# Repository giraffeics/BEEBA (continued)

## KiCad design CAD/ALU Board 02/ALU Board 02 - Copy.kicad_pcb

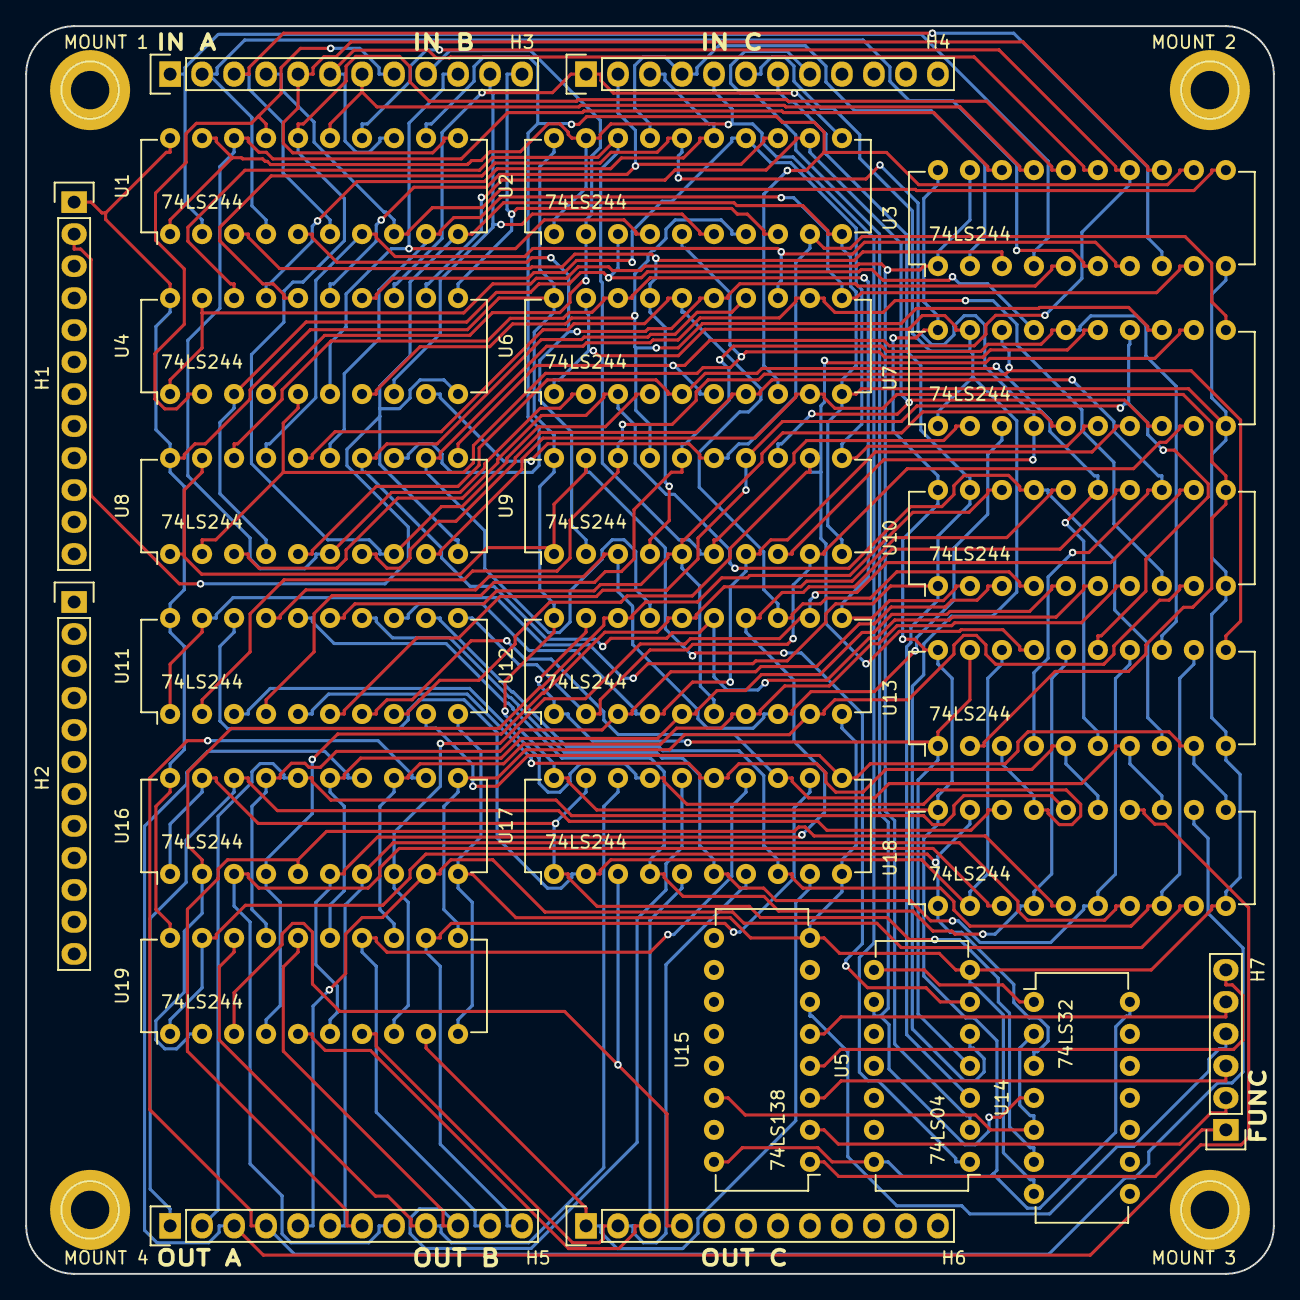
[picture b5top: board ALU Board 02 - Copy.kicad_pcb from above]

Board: 2 copper layers, 99.1 x 99.1 mm, 30 parts (0 on the bottom side), 99 nets.

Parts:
H1, H2, H3, H4, H5, H6: CONN_01X12; Socket_Strip_Straight_1x12
H7: CONN_01X06; Socket_Strip_Straight_1x06
MOUNT 1, MOUNT 2, MOUNT 3, MOUNT 4: 1pin
U1, U2, U3, U4, U6, U7, U8, U9, U10, U11, U12, U13, U16, U17, U18, U19: 74LS244; DIP-20_W7.62mm
U5: 74LS04; DIP-14_W7.62mm
U14: 74LS32; DIP-14_W7.62mm
U15: 74LS138; DIP-16_W7.62mm

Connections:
FS09: U14.2, U14.5, U15.14
FUNC0: H7.1, U15.1
FUNC1: H7.2, U15.2
FUNC2: H7.3, U15.3
FUNC3: H7.4, U15.6
FUNC4: H7.5, U15.5
FUNC5: H7.6, U15.4
GND: H1.2, U1.10, U2.10, U3.10, U4.10, U5.7, U6.10, U7.10, U8.10, U9.10, U10.10, U11.10, U12.10, U13.10, U14.7, U15.8, U16.10, U17.10, U18.10, U19.10
INA0: H3.1, U1.2, U3.4
INA1: H3.2, U1.4, U3.6
INA2: H3.3, U1.6, U3.8
INA3: H3.4, U1.8, U3.11
INA4: H3.5, U1.11, U3.13
INA5: H3.6, U1.13, U3.15
INA6: H3.7, U1.15, U3.17
INA7: H3.8, U1.17, U4.2
INB0: H3.9, U2.2, U4.4
INB1: H3.10, U2.4, U4.6
INB2: H3.11, U2.6, U4.8
INB3: H3.12, U2.8, U4.11
INB4: H4.1, U2.11, U4.13
INB5: H4.2, U2.13, U4.15
INB6: H4.3, U2.15, U4.17
INB7: H4.4, U2.17, U3.2
INC0: H4.5, U1.1, U1.19, U2.1, U2.19, U5.1
INC1: H4.6, U5.5, U6.1, U6.19, U7.1, U7.19
INC2: H4.7, U5.3, U10.1, U10.19, U11.1, U11.19
INC3: H4.8, U5.9, U14.4
NINC0: U3.1, U3.19, U4.1, U4.19, U5.2
NINC1: U5.6, U8.1, U8.19, U9.1, U9.19
NINC2: U5.4, U12.1, U12.19, U13.1, U13.19
NINC3: U14.3, U18.1, U18.19, U19.1, U19.19
unnamed: U5.8, U14.1
OUTA0: H5.1, U16.18, U18.18
OUTA1: H5.2, U16.16, U18.16
OUTA2: H5.3, U16.14, U18.14
OUTA3: H5.4, U16.12, U18.12
OUTA4: H5.5, U16.9, U18.9
OUTA5: H5.6, U16.7, U18.7
OUTA6: H5.7, U16.5, U18.5
OUTA7: H5.8, U16.3, U18.3
OUTB0: H5.9, U17.18, U19.18
OUTB1: H5.10, U17.16, U19.16
OUTB2: H5.11, U17.14, U19.14
OUTB3: H5.12, U17.12, U19.12
OUTB4: H6.1, U17.9, U19.9
OUTB5: H6.2, U17.7, U19.7
OUTB6: H6.3, U17.5, U19.5
OUTB7: H6.4, U17.3, U19.3
SHA00: U1.18, U3.18, U6.2, U8.6
SHA01: U1.16, U3.16, U6.4, U8.8
SHA02: U1.14, U3.14, U6.6, U8.11
SHA03: U1.12, U3.12, U6.8, U8.13
SHA04: U1.9, U3.9, U6.11, U8.15
SHA05: U1.7, U3.7, U6.13, U8.17
SHA06: U1.5, U3.5, U6.15, U9.2
SHA07: U1.3, U3.3, U6.17, U9.4
SHA08: U2.18, U4.18, U7.2, U9.6
SHA09: U2.16, U4.16, U7.4, U9.8
SHA10: U2.14, U4.14, U7.6, U9.11
SHA11: U2.12, U4.12, U7.8, U9.13
SHA12: U2.9, U4.9, U7.11, U9.15
SHA13: U2.7, U4.7, U7.13, U9.17
SHA14: U2.5, U4.5, U7.15, U8.2
SHA15: U2.3, U4.3, U7.17, U8.4
SHB00: U6.18, U8.18, U10.2, U12.11
SHB01: U6.16, U8.16, U10.4, U12.13
SHB02: U6.14, U8.14, U10.6, U12.15
SHB03: U6.12, U8.12, U10.8, U12.17
SHB04: U6.9, U8.9, U10.11, U13.2
SHB05: U6.7, U8.7, U10.13, U13.4
SHB06: U6.5, U8.5, U10.15, U13.6
SHB07: U6.3, U8.3, U10.17, U13.8
SHB08: U7.18, U9.18, U11.2, U13.11
SHB09: U7.16, U9.16, U11.4, U13.13
SHB10: U7.14, U9.14, U11.6, U13.15
SHB11: U7.12, U9.12, U11.8, U13.17
SHB12: U7.9, U9.9, U11.11, U12.2
SHB13: U7.7, U9.7, U11.13, U12.4
SHB14: U7.5, U9.5, U11.15, U12.6
SHB15: U7.3, U9.3, U11.17, U12.8
SHC00: U10.18, U12.18, U16.2, U19.2
SHC01: U10.16, U12.16, U16.4, U19.4
SHC02: U10.14, U12.14, U16.6, U19.6
SHC03: U10.12, U12.12, U16.8, U19.8
SHC04: U10.9, U12.9, U16.11, U19.11
SHC05: U10.7, U12.7, U16.13, U19.13
SHC06: U10.5, U12.5, U16.15, U19.15
SHC07: U10.3, U12.3, U16.17, U19.17
SHC08: U11.18, U13.18, U17.2, U18.2
SHC09: U11.16, U13.16, U17.4, U18.4
SHC10: U11.14, U13.14, U17.6, U18.6
SHC11: U11.12, U13.12, U17.8, U18.8
SHC12: U11.9, U13.9, U17.11, U18.11
SHC13: U11.7, U13.7, U17.13, U18.13
SHC14: U11.5, U13.5, U17.15, U18.15
SHC15: U11.3, U13.3, U17.17, U18.17
VCC: H1.1, U1.20, U2.20, U3.20, U4.20, U5.14, U6.20, U7.20, U8.20, U9.20, U10.20, U11.20, U12.20, U13.20, U14.14, U15.16, U16.20, U17.20, U18.20, U19.20
YINC3: U14.6, U16.1, U16.19, U17.1, U17.19

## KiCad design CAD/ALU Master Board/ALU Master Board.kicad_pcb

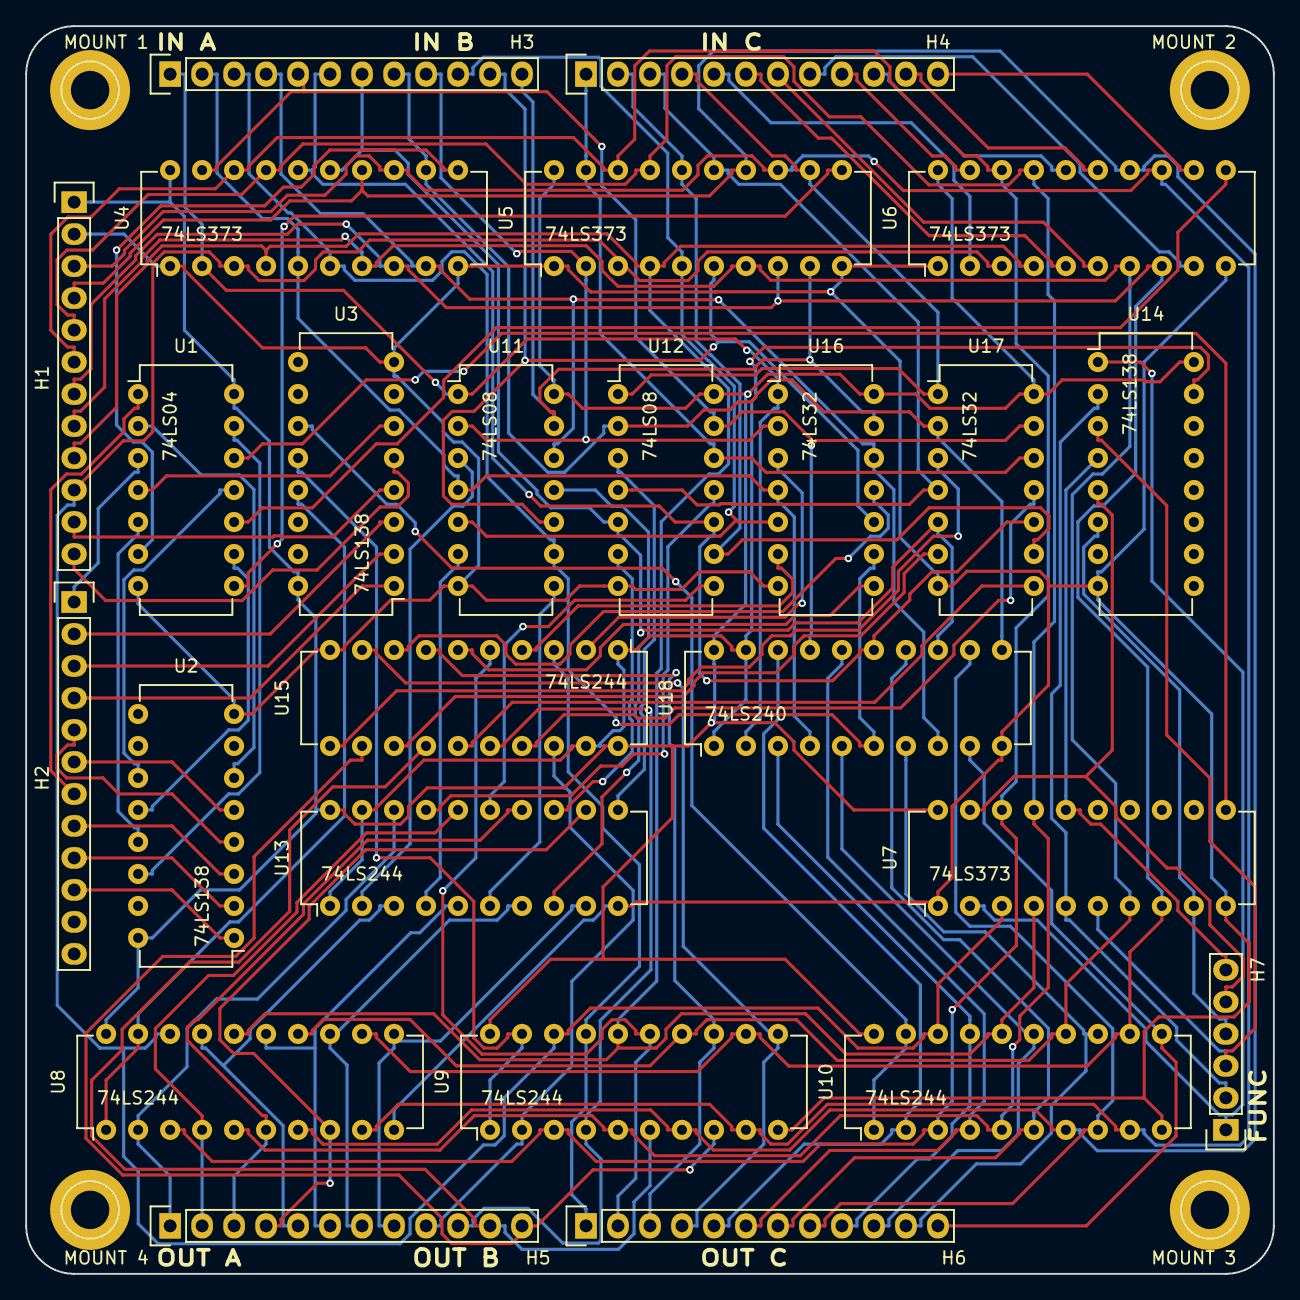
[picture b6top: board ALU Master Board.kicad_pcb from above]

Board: 2 copper layers, 99.1 x 99.1 mm, 29 parts (0 on the bottom side), 106 nets.

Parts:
H1, H2, H3, H4, H5, H6: CONN_01X12; Socket_Strip_Straight_1x12
H7: CONN_01X06; Socket_Strip_Straight_1x06
MOUNT 1, MOUNT 2, MOUNT 3, MOUNT 4: 1pin
U1: 74LS04; DIP-14_W7.62mm
U2, U3, U14: 74LS138; DIP-16_W7.62mm
U4, U5, U6, U7: 74LS373; DIP-20_W7.62mm
U8, U9, U10, U13, U15: 74LS244; DIP-20_W7.62mm
U11, U12: 74LS08; DIP-14_W7.62mm
U16, U17: 74LS32; DIP-14_W7.62mm
U18: 74LS240; DIP-20_W7.62mm

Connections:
DATA0: H1.10, U4.3, U5.3, U6.3, U7.3, U8.18, U9.18, U10.18
DATA1: H1.9, U4.4, U5.4, U6.4, U7.4, U8.16, U9.16, U10.16
DATA2: H1.8, U4.7, U5.7, U6.7, U7.7, U8.14, U9.14, U10.14
DATA3: H1.7, U4.8, U5.8, U6.8, U7.8, U8.12, U9.12, U10.12
DATA4: H1.6, U4.18, U5.18, U6.18, U7.18, U8.3, U9.3, U10.3
DATA5: H1.5, U4.17, U5.17, U6.17, U7.17, U8.5, U9.5, U10.5
DATA6: H1.4, U4.14, U5.14, U6.14, U8.7, U9.7, U10.7
DATA7: H1.3, U4.13, U5.13, U6.13, U8.9, U9.9, U10.9
FS08: U13.1, U13.19, U14.15, U15.1, U15.19, U18.1, U18.19
FUNC0: H7.1, U7.2, U14.1
FUNC1: H7.2, U7.5, U14.2
FUNC2: H7.3, U7.6, U14.3
FUNC3: H7.4, U7.9, U14.6
FUNC4: H7.5, U7.19, U14.5
FUNC5: H7.6, U7.16, U14.4
GND: H1.2, U1.7, U2.8, U3.8, U4.1, U4.10, U5.1, U5.10, U6.1, U6.10, U7.1, U7.10, U8.10, U9.10, U10.10, U11.7, U12.7, U13.10, U14.8, U15.10, U16.7, U17.7, U18.10
INA0: H3.1, U4.2, U11.1, U16.1, U18.2
INA1: H3.2, U4.5, U11.4, U16.4, U18.4
INA2: H3.3, U4.6, U11.9, U16.9, U18.6
INA3: H3.4, U4.9, U11.12, U16.12, U18.8
INA4: H3.5, U4.19, U12.13, U17.13, U18.17
INA5: H3.6, U4.16, U12.10, U17.10, U18.15
INA6: H3.7, U4.15, U12.5, U17.5, U18.13
INA7: H3.8, U4.12, U12.2, U17.2, U18.11
INB0: H3.9, U5.2, U11.2, U16.2
INB1: H3.10, U5.5, U11.5, U16.5
INB2: H3.11, U5.6, U11.10, U16.10
INB3: H3.12, U5.9, U11.13, U16.13
INB4: H4.1, U5.19, U12.12, U17.12
INB5: H4.2, U5.16, U12.9, U17.9
INB6: H4.3, U5.15, U12.4, U17.4
INB7: H4.4, U5.12, U12.1, U17.1
INC0: H4.5, U6.2
INC1: H4.6, U6.5
INC2: H4.7, U6.6
INC3: H4.8, U6.9
INC4: H4.9, U6.19
INC5: H4.10, U6.16
INC6: H4.11, U6.15
INC7: H4.12, U6.12
unnamed: U1.2, U2.6
unnamed: U1.4, U3.6
unnamed: U1.6, U4.11
unnamed: U1.8, U5.11
unnamed: U1.10, U6.11
unnamed: U1.12, U7.11
unnamed: U11.3, U13.2
unnamed: U11.6, U13.4
unnamed: U11.8, U13.6
unnamed: U11.11, U13.8
unnamed: U12.3, U13.11
unnamed: U12.6, U13.13
unnamed: U12.8, U13.15
unnamed: U12.11, U13.17
unnamed: U15.2, U16.3
unnamed: U15.4, U16.6
unnamed: U15.6, U16.8
unnamed: U15.8, U16.11
unnamed: U15.11, U17.3
unnamed: U15.13, U17.6
unnamed: U15.15, U17.8
unnamed: U15.17, U17.11
OUTA0: H5.1, U8.2, U13.18
OUTA1: H5.2, U8.4, U13.16
OUTA2: H5.3, U8.6, U13.14
OUTA3: H5.4, U8.8, U13.12
OUTA4: H5.5, U8.17, U13.3
OUTA5: H5.6, U8.15, U13.5
OUTA6: H5.7, U8.13, U13.7
OUTA7: H5.8, U8.11, U13.9
OUTB0: H5.9, U9.2, U15.18
OUTB1: H5.10, U9.4, U15.16
OUTB2: H5.11, U9.6, U15.14
OUTB3: H5.12, U9.8, U15.12
OUTB4: H6.1, U9.17, U15.3
OUTB5: H6.2, U9.15, U15.5
OUTB6: H6.3, U9.13, U15.7
OUTB7: H6.4, U9.11, U15.9
OUTC0: H6.5, U10.2, U18.18
OUTC1: H6.6, U10.4, U18.16
OUTC2: H6.7, U10.6, U18.14
OUTC3: H6.8, U10.8, U18.12
OUTC4: H6.9, U10.17, U18.3
OUTC5: H6.10, U10.15, U18.5
OUTC6: H6.11, U10.13, U18.7
OUTC7: H6.12, U10.11, U18.9
READ0: H2.4, U3.1
READ1: H2.3, U3.2
READ2: H2.2, U3.3
READ3: H2.1, U1.3
READ4: H1.12, U3.5
READ5: H1.11, U3.4
RS02: U3.13, U8.1, U8.19
RS03: U3.12, U9.1, U9.19
RS04: U3.11, U10.1, U10.19
VCC: H1.1, U1.14, U2.16, U3.16, U4.20, U5.20, U6.20, U7.20, U8.20, U9.20, U10.20, U11.14, U12.14, U13.20, U14.16, U15.20, U16.14, U17.14, U18.20
WRITE0: H2.10, U2.1
WRITE1: H2.9, U2.2
WRITE2: H2.8, U2.3
WRITE3: H2.7, U1.1
WRITE4: H2.6, U2.5
WRITE5: H2.5, U2.4
WS01: U1.13, U2.14
WS02: U1.5, U2.13
WS03: U1.9, U2.12
WS04: U1.11, U2.11

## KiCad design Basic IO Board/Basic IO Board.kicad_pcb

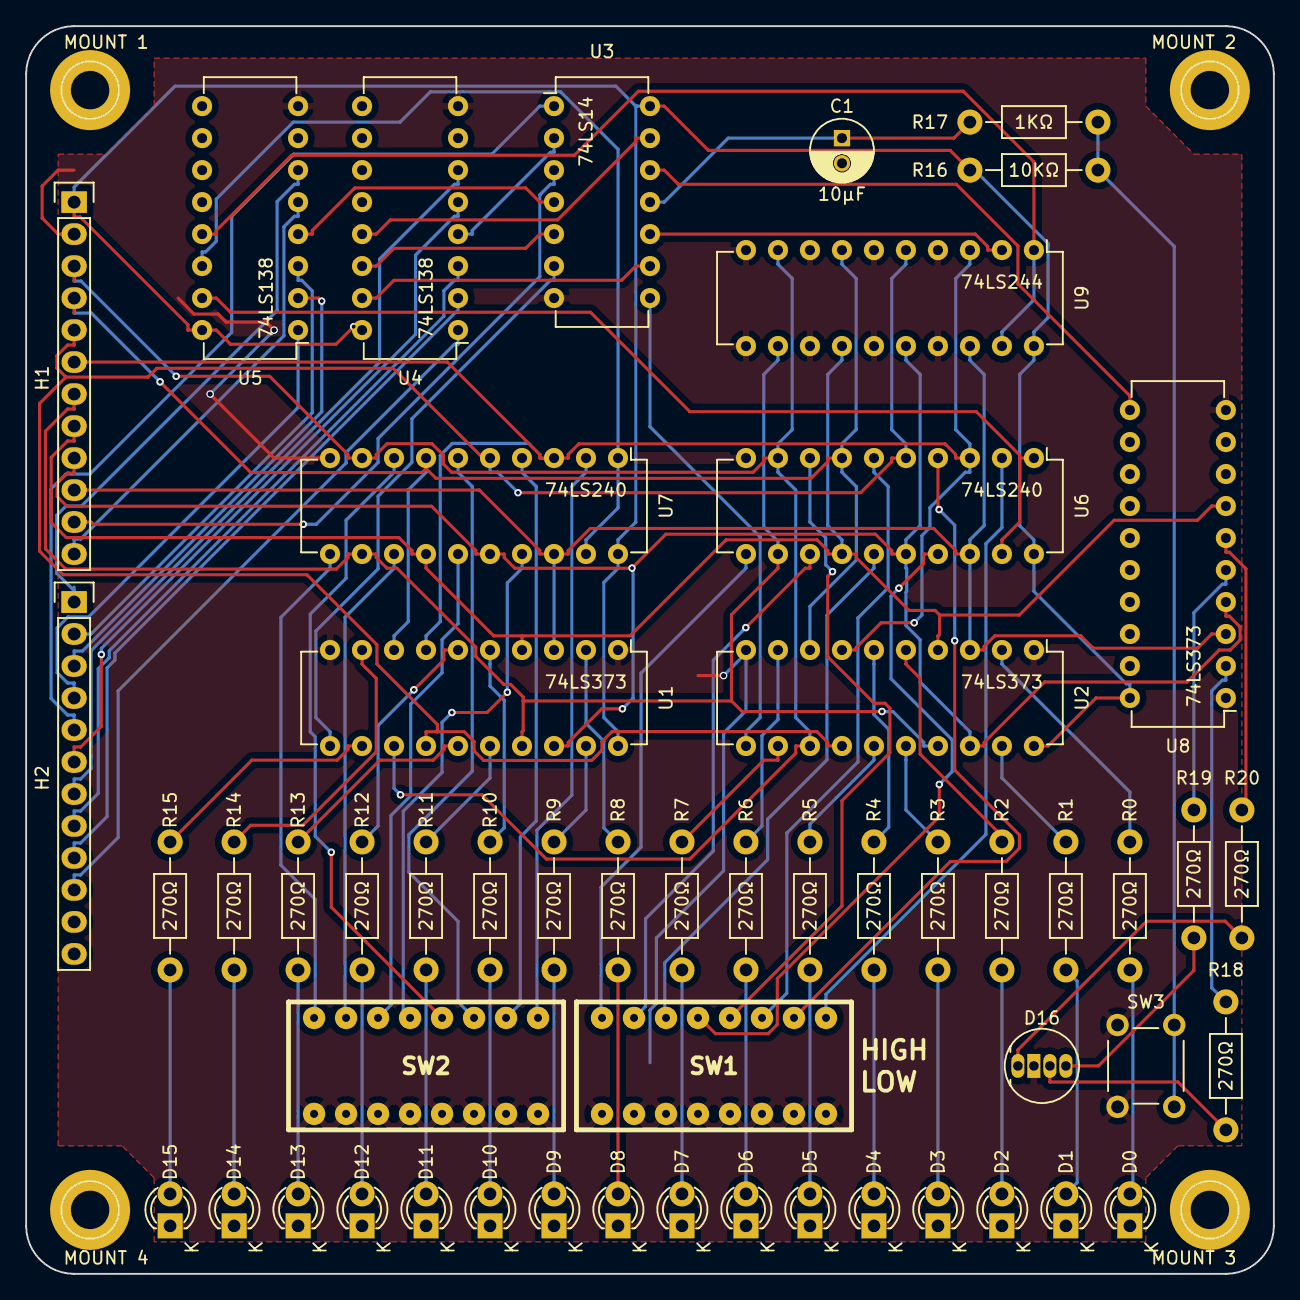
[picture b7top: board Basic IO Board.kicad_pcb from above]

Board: 2 copper layers, 99.1 x 99.1 mm, 57 parts (0 on the bottom side), 90 nets.

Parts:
C1: 10µF; C_Radial_D5_L11_P2
D0, D1, D2, D3, D4, D5, D6, D7, D8, D9, D10, D11, D12, D13, D14, D15: Led_Small; LED-3MM
D16: LED_RCBG; LED-RGB-5MM_Common_Cathode
H1, H2: CONN_01X12; Socket_Strip_Straight_1x12
MOUNT 1, MOUNT 2, MOUNT 3, MOUNT 4: 1pin
R0, R1, R2, R3, R4, R5, R6, R7, R8, R9, R10, R11, R12, R13, R14, R15, R18, R19, R20: 270Ω; Resistor_Horizontal_RM10mm
R16: 10KΩ; Resistor_Horizontal_RM10mm
R17: 1KΩ; Resistor_Horizontal_RM10mm
SW1, SW2: DIPS_08; DIPS-DS08
SW3: SW_PUSH; switch_tactile_6mm
U1, U2, U8: 74LS373; DIP-20_W7.62mm
U3: 74LS14; DIP-14_W7.62mm
U4, U5: 74LS138; DIP-16_W7.62mm
U6, U7: 74LS240; DIP-20_W7.62mm
U9: 74LS244; DIP-20_W7.62mm

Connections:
DATA0: H1.10, U1.3, U2.3, U6.18, U7.18, U8.3, U9.18
DATA1: H1.9, U1.18, U2.18, U6.16, U7.16, U8.4, U9.16
DATA2: H1.8, U1.4, U2.4, U6.14, U7.14, U8.7, U9.14
DATA3: H1.7, U1.17, U2.17, U6.12, U7.12, U9.12
DATA4: H1.6, U1.7, U2.7, U6.3, U7.3, U9.3
DATA5: H1.5, U1.14, U2.14, U6.5, U7.5, U9.5
DATA6: H1.4, U1.8, U2.8, U6.7, U7.7, U9.7
DATA7: H1.3, U1.13, U2.13, U6.9, U7.9, U9.9
GND: C1.2, D0.1, D1.1, D2.1, D3.1, D4.1, D5.1, D6.1, D7.1, D8.1, D9.1, D10.1, D11.1, D12.1, D13.1, D14.1, D15.1, D16.2, H1.2, SW1.9, SW1.10, SW1.11, SW1.12, SW1.13, SW1.14, SW1.15, SW1.16, SW2.9, SW2.10, SW2.11, SW2.12, SW2.13, SW2.14, SW2.15, SW2.16, SW3.1, U1.1, U1.10, U2.1, U2.10, U3.7, U4.8, U5.8, U6.10, U7.10, U8.1, U8.10, U9.4, U9.6, U9.8, U9.10, U9.11, U9.13, U9.15, U9.17
unnamed: C1.1, R17.1, U3.11
unnamed: D0.2, R0.2
unnamed: D1.2, R1.2
unnamed: D2.2, R2.2
unnamed: D3.2, R3.2
unnamed: D4.2, R4.2
unnamed: D5.2, R5.2
unnamed: D6.2, R6.2
unnamed: D7.2, R7.2
unnamed: D8.2, R8.2
unnamed: D9.2, R9.2
unnamed: D10.2, R10.2
unnamed: D11.2, R11.2
unnamed: D12.2, R12.2
unnamed: D13.2, R13.2
unnamed: D14.2, R14.2
unnamed: D15.2, R15.2
unnamed: D16.1, R20.1
unnamed: D16.3, R18.1
unnamed: D16.4, R19.1
unnamed: R0.1, U2.2
unnamed: R1.1, U2.19
unnamed: R2.1, U2.5
unnamed: R3.1, U2.16
unnamed: R4.1, U2.6
unnamed: R5.1, U2.15
unnamed: R6.1, U2.9
unnamed: R7.1, U2.12
unnamed: R8.1, U1.2
unnamed: R9.1, U1.19
unnamed: R10.1, U1.5
unnamed: R11.1, U1.16
unnamed: R12.1, U1.6
unnamed: R13.1, U1.15
unnamed: R14.1, U1.9
unnamed: R15.1, U1.12
unnamed: R16.2, R17.2, SW3.2
unnamed: R18.2, U8.2
unnamed: R19.2, U8.5
unnamed: R20.2, U8.6
unnamed: SW1.1, U6.2
unnamed: SW1.2, U6.4
unnamed: SW1.3, U6.6
unnamed: SW1.4, U6.8
unnamed: SW1.5, U6.17
unnamed: SW1.6, U6.15
unnamed: SW1.7, U6.13
unnamed: SW1.8, U6.11
unnamed: SW2.1, U7.2
unnamed: SW2.2, U7.4
unnamed: SW2.3, U7.6
unnamed: SW2.4, U7.8
unnamed: SW2.5, U7.17
unnamed: SW2.6, U7.15
unnamed: SW2.7, U7.13
unnamed: SW2.8, U7.11
unnamed: U1.11, U3.6
unnamed: U2.11, U3.8
unnamed: U3.2, U4.4
unnamed: U3.4, U5.4
unnamed: U3.10, U9.2
unnamed: U3.12, U8.11
READ0: H2.4, U5.1
READ1: H2.3, U5.2
READ2: H2.2, U5.3
READ3: H2.1, U5.6
READ4: H1.12, U5.5
READ5: H1.11, U3.3
RS40: U5.15, U6.1, U6.19
RS41: U5.14, U7.1, U7.19
RS42: U5.13, U9.1, U9.19
VCC: H1.1, R16.1, U1.20, U2.20, U3.14, U4.16, U5.16, U6.20, U7.20, U8.20, U9.20
WRITE0: H2.10, U4.1
WRITE1: H2.9, U4.2
WRITE2: H2.8, U4.3
WRITE3: H2.7, U4.6
WRITE4: H2.6, U4.5
WRITE5: H2.5, U3.1
WS40: U3.9, U4.15
WS41: U3.5, U4.14
WS42: U3.13, U4.13

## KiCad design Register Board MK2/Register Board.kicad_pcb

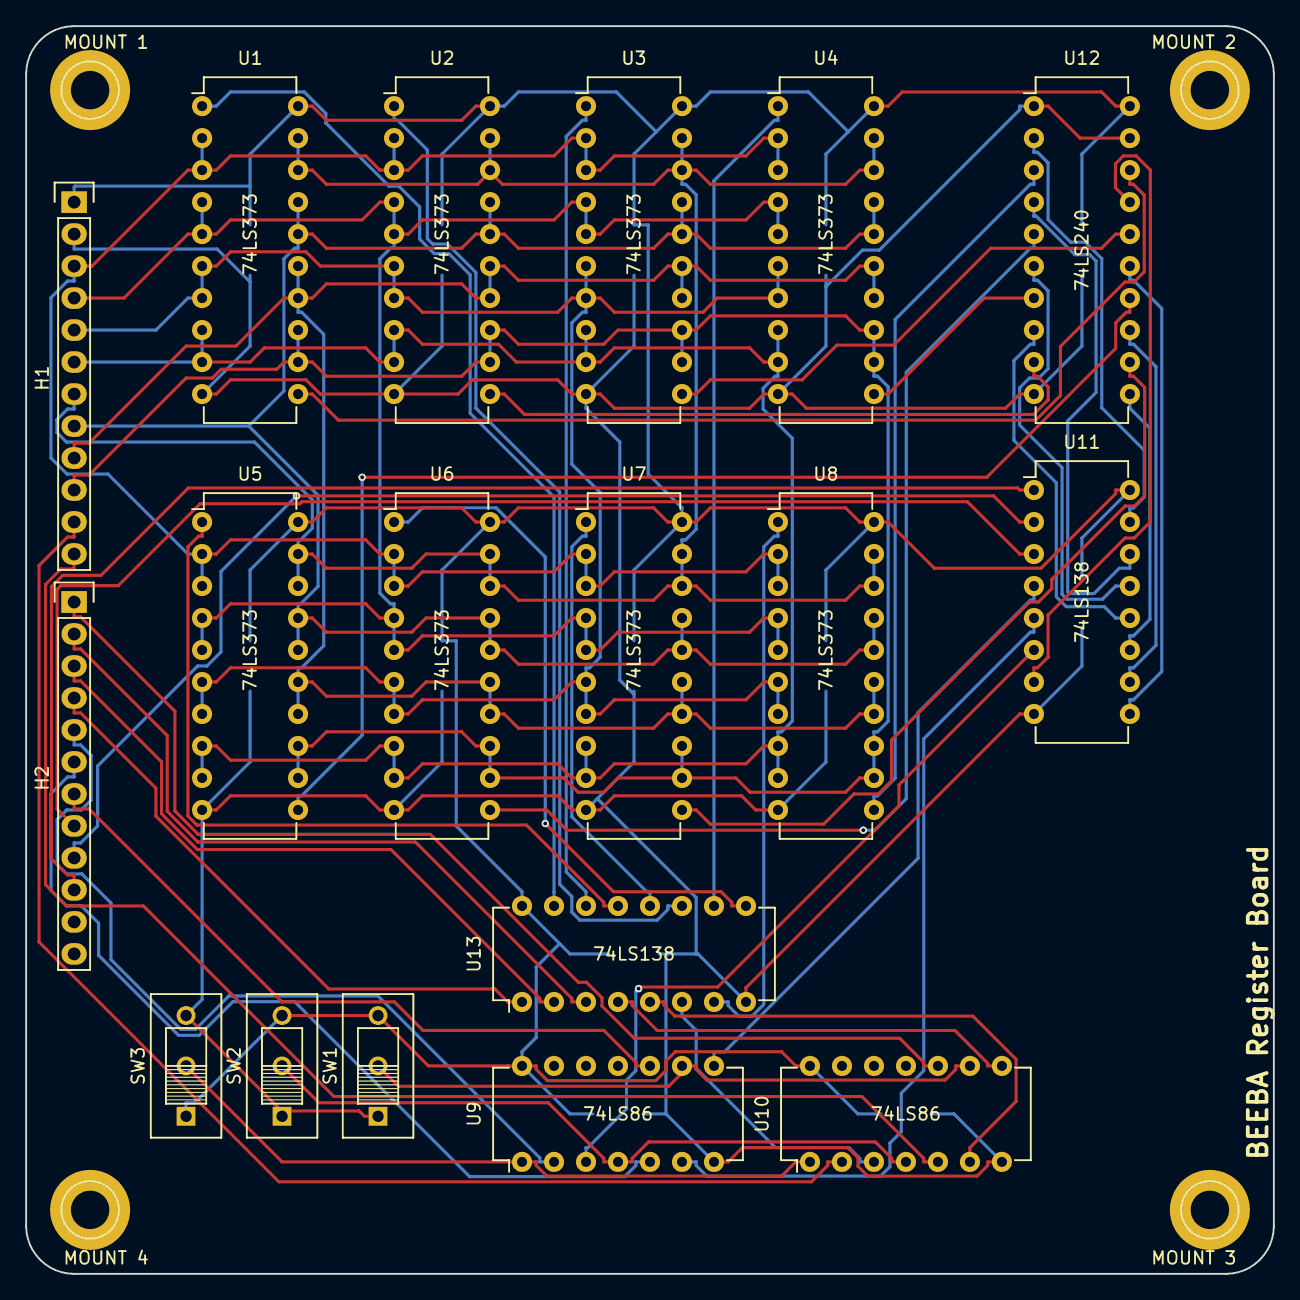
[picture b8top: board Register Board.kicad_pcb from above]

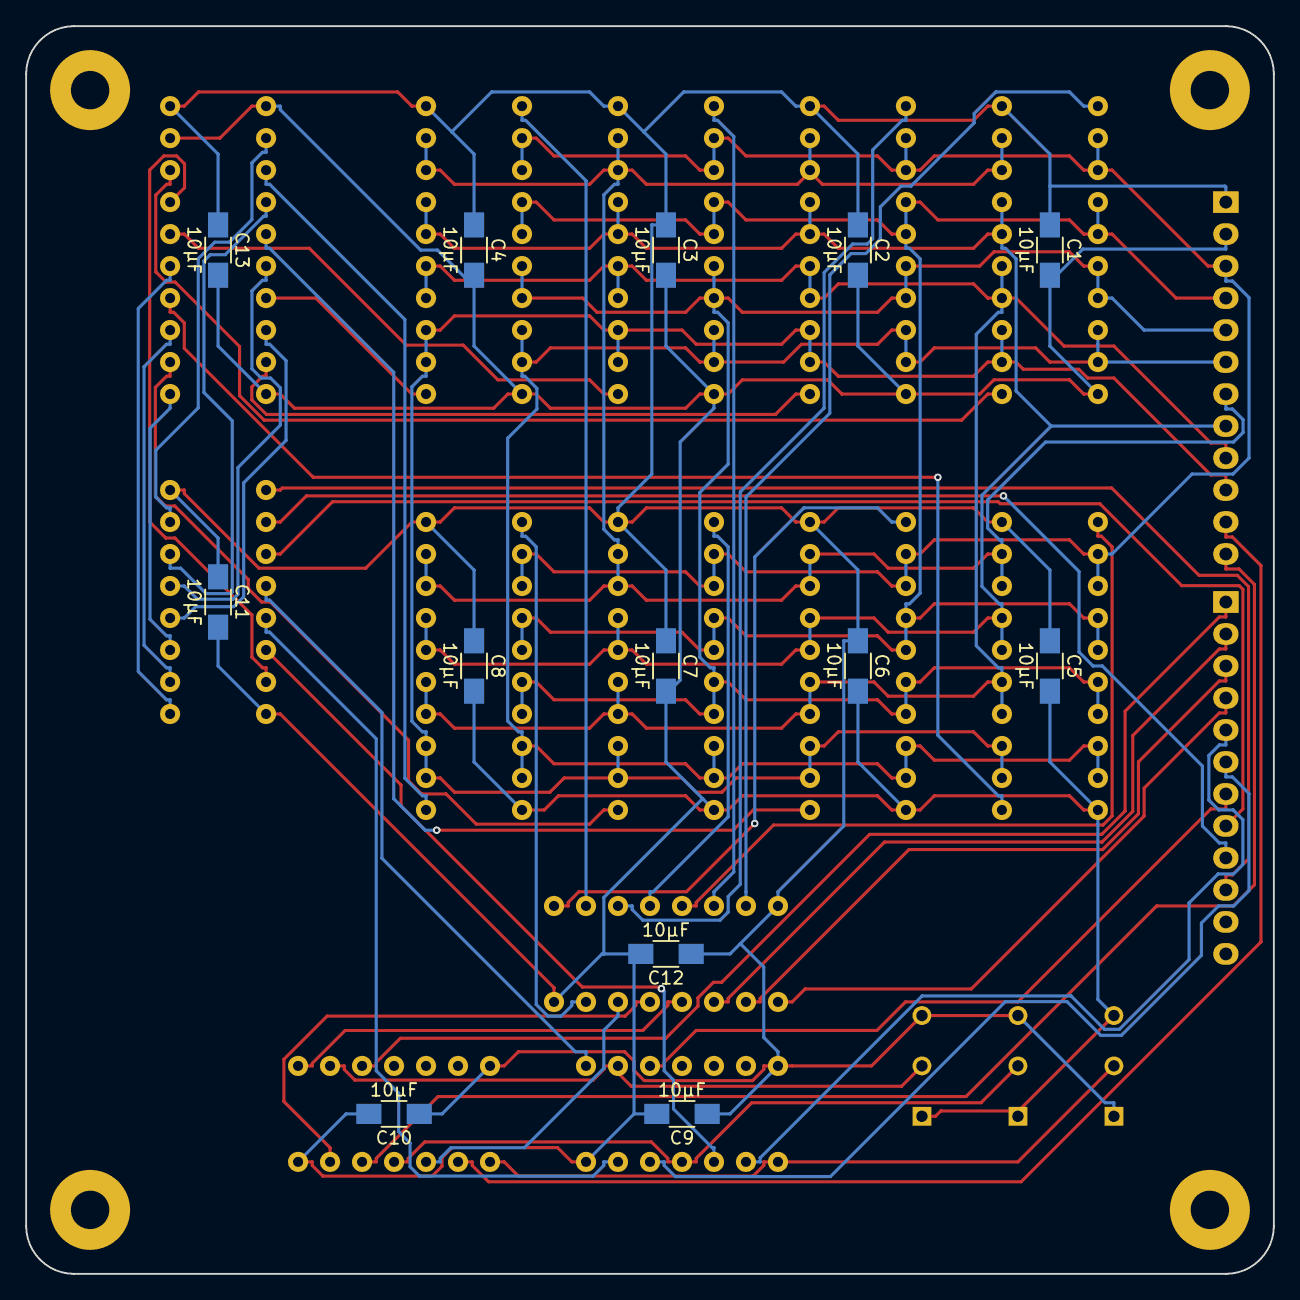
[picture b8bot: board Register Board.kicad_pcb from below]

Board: 2 copper layers, 99.1 x 99.1 mm, 35 parts (13 on the bottom side), 55 nets.

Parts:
C1, C2, C3, C4, C5, C6, C7, C8, C9, C10, C11, C12, C13: 10µF; C_1206_HandSoldering
H1, H2: CONN_01X12; Socket_Strip_Straight_1x12
MOUNT 1, MOUNT 2, MOUNT 3, MOUNT 4: 1pin
SW1, SW2, SW3: SWITCH_INV; SW_SPST_4mm_holes
U1, U2, U3, U4, U5, U6, U7, U8: 74LS373; DIP-20_W7.62mm
U9, U10: 74LS86; DIP-14_W7.62mm
U11, U13: 74LS138; DIP-16_W7.62mm
U12: 74LS240; DIP-20_W7.62mm

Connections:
DATA0: H1.10, U1.12, U1.13, U2.12, U2.13, U3.12, U3.13, U4.12, U4.13, U5.12, U5.13, U6.12, U6.13, U7.12, U7.13, U8.12, U8.13
DATA1: H1.9, U1.14, U1.15, U2.14, U2.15, U3.14, U3.15, U4.14, U4.15, U5.14, U5.15, U6.14, U6.15, U7.14, U7.15, U8.14, U8.15
DATA2: H1.8, U1.16, U1.17, U2.16, U2.17, U3.16, U3.17, U4.16, U4.17, U5.16, U5.17, U6.16, U6.17, U7.16, U7.17, U8.16, U8.17
DATA3: H1.7, U1.18, U1.19, U2.18, U2.19, U3.18, U3.19, U4.18, U4.19, U5.18, U5.19, U6.18, U6.19, U7.18, U7.19, U8.18, U8.19
DATA4: H1.6, U1.8, U1.9, U2.8, U2.9, U3.8, U3.9, U4.8, U4.9, U5.8, U5.9, U6.8, U6.9, U7.8, U7.9, U8.8, U8.9
DATA5: H1.5, U1.6, U1.7, U2.6, U2.7, U3.6, U3.7, U4.6, U4.7, U5.6, U5.7, U6.6, U6.7, U7.6, U7.7, U8.6, U8.7
DATA6: H1.4, U1.4, U1.5, U2.4, U2.5, U3.4, U3.5, U4.4, U4.5, U5.4, U5.5, U6.4, U6.5, U7.4, U7.5, U8.4, U8.5
DATA7: H1.3, U1.2, U1.3, U2.2, U2.3, U3.2, U3.3, U4.2, U4.3, U5.2, U5.3, U6.2, U6.3, U7.2, U7.3, U8.2, U8.3
GND: C1.2, C2.2, C3.2, C4.2, C5.2, C6.2, C7.2, C8.2, C9.2, C10.2, C11.2, C12.2, C13.2, H1.2, SW1.1, SW2.1, SW3.3, U1.10, U2.10, U3.10, U4.10, U5.10, U6.10, U7.10, U8.10, U9.7, U10.7, U11.8, U12.1, U12.10, U12.19, U13.8
unnamed: U10.3, U13.6
unnamed: U10.6, U13.5
unnamed: U10.8, U13.4
unnamed: U9.8, U11.4
unnamed: U9.6, U11.5
unnamed: U9.3, U11.6
unnamed: U11.7, U12.17
unnamed: U11.9, U12.15
unnamed: U11.10, U12.13
unnamed: U11.11, U12.11
unnamed: U11.12, U12.8
unnamed: U11.13, U12.6
unnamed: U11.14, U12.4
unnamed: U11.15, U12.2
RE0: U1.1, U13.15
RE1: U3.1, U13.14
RE2: U5.1, U13.13
RE3: U7.1, U13.12
RE4: U2.1, U13.11
RE5: U4.1, U13.10
RE6: U6.1, U13.9
RE7: U8.1, U13.7
READ0: H2.4, U13.1
READ1: H2.3, U13.2
READ2: H2.2, U13.3
READ3: H2.1, U10.10
READ4: H1.12, U10.5
READ5: H1.11, U10.2
SEL1: SW1.2, U9.9, U10.9
SEL2: SW2.2, U9.4, U10.4
SEL3: SW3.2, U9.1, U10.1
VCC: C1.1, C2.1, C3.1, C4.1, C5.1, C6.1, C7.1, C8.1, C9.1, C10.1, C11.1, C12.1, C13.1, H1.1, SW1.3, SW2.3, SW3.1, U1.20, U2.20, U3.20, U4.20, U5.20, U6.20, U7.20, U8.20, U9.14, U10.14, U11.16, U12.20, U13.16
WE0: U1.11, U12.18
WE1: U3.11, U12.16
WE2: U5.11, U12.14
WE3: U7.11, U12.12
WE4: U2.11, U12.9
WE5: U4.11, U12.7
WE6: U6.11, U12.5
WE7: U8.11, U12.3
WRITE0: H2.10, U11.1
WRITE1: H2.9, U11.2
WRITE2: H2.8, U11.3
WRITE3: H2.7, U9.10
WRITE4: H2.6, U9.5
WRITE5: H2.5, U9.2

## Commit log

2017-10-14 add design files, .gitignore
    Added files to the empty repository.
2017-10-14 move CAD files, add assembler, write README
    Moved CAD files to the "CAD" folder. Added the assembler to the project. Wrote some documentation in README.md.
2017-10-14 fix README.md
    Replaced greater than / less than characters with square brackets to avoid those characters being interpreted as HTML tags.
